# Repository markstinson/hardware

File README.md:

Internal OPL3 ISA 8 bits

version 1.0

With problems still unidentified. The schematic is based on texelec board Resound v1.1:

https://texelec.com/product/resound-opl3-4-channel-opl3-sound-card-8-bit-isa/

Symptoms:

The first start is always correct, it works and you can hear it perfectly, clear FM OPL3 sound ... but after approximately 2 minutes, it stops working. Normally a sleep period without connecting makes it work again, but there have been cases in which it stops working forever... it seems some kind of overload.

The ICs or components do not look hot, and the voltage tracks are not larger than the rest of the signals, this could be an error, however the width of the same should be sufficient for the mA demand of the ICs (I think) .

Another theory is that I do not use electrolytic 10uF capacitors as in the original design, they are 10uF without polarity, but in principle I think that should not affect the operation.

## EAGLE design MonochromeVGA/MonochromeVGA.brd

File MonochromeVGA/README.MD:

# Description

MonochromeVGA is a product to enjoy the charm of those monochrome monitors of the time but in the current video systems, and more specifically in your PC monitor. Although it could be connected to any TV, monitor or video system that has VGA inputs.

Select green, amber or B&W as monochromatic color, among others. Change color to monochrome or vice versa easily.

https://hackaday.io/project/166041-monochromevga

Disclaimer:

It is recommended to use MonochromeVGA inside an shielded container, which can be as simple as a cardboard box lined with aluminium foil, because although unlikely, the VGA signal could interfere with other nearby devices and depending on the laws of your country, it could lead to fines.

In any case, use any hardware posted here at your own risk.

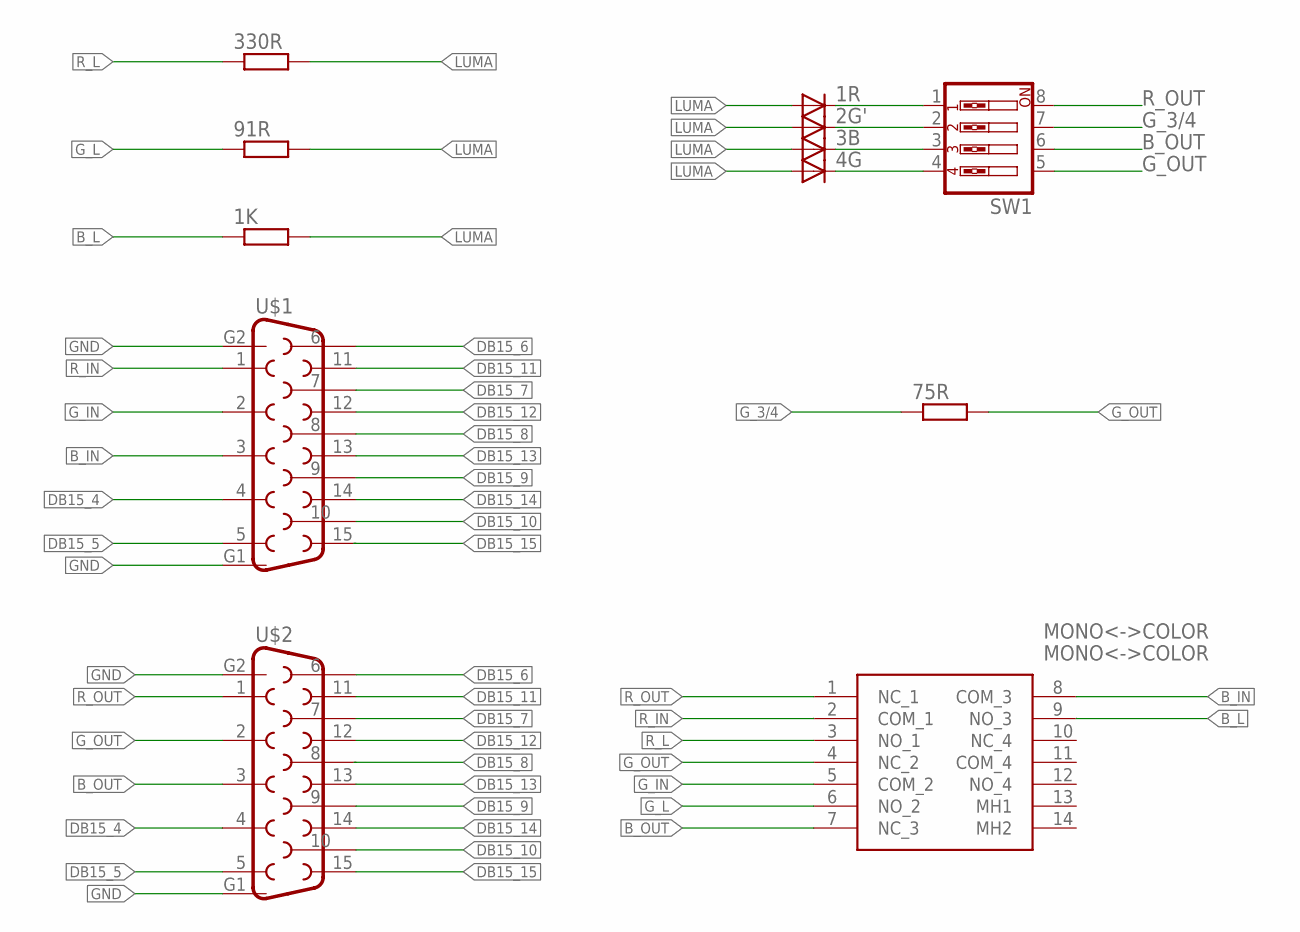
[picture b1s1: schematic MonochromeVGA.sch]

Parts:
1K, 75R, 91R, 330R: R-EU_0204/5; 0204/5
1R, 2G', 3B, 4G: DIODE-D-5; D-5
MONO<->COLOR: MONO<->COLOR; EG4208A
SW1: SW_DIP-4; EDG-04
U$1, U$2: DB15

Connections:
B_IN: MONO<->COLOR.8 (COM_3), U$1.3
B_L: 1K.1, MONO<->COLOR.9 (NO_3)
B_OUT: MONO<->COLOR.7 (NC_3), SW1.6, U$2.3
DB15_4: U$1.4, U$2.4
DB15_5: U$1.5, U$2.5
DB15_6: U$1.6, U$2.6
DB15_7: U$1.7, U$2.7
DB15_8: U$1.8, U$2.8
DB15_9: U$1.9, U$2.9
DB15_10: U$1.10, U$2.10
DB15_11: U$1.11, U$2.11
DB15_12: U$1.12, U$2.12
DB15_13: U$1.13, U$2.13
DB15_14: U$1.14, U$2.14
DB15_15: U$1.15, U$2.15
GND: U$1.G1 (G2), U$1.G2 (G1), U$2.G1 (G2), U$2.G2 (G1)
G_3/4: 75R.1, SW1.7
G_IN: MONO<->COLOR.5 (COM_2), U$1.2
G_L: 91R.1, MONO<->COLOR.6 (NO_2)
G_OUT: 75R.2, MONO<->COLOR.4 (NC_2), SW1.5, U$2.2
LUMA: 1K.2, 1R.A, 2G'.A, 3B.A, 4G.A, 91R.2, 330R.2
unnamed: 2G'.C, SW1.2
unnamed: 3B.C, SW1.3
unnamed: 4G.C, SW1.4
unnamed: 1R.C, SW1.1
R_IN: MONO<->COLOR.2 (COM_1), U$1.1
R_L: 330R.1, MONO<->COLOR.3 (NO_1)
R_OUT: MONO<->COLOR.1 (NC_1), SW1.8, U$2.1

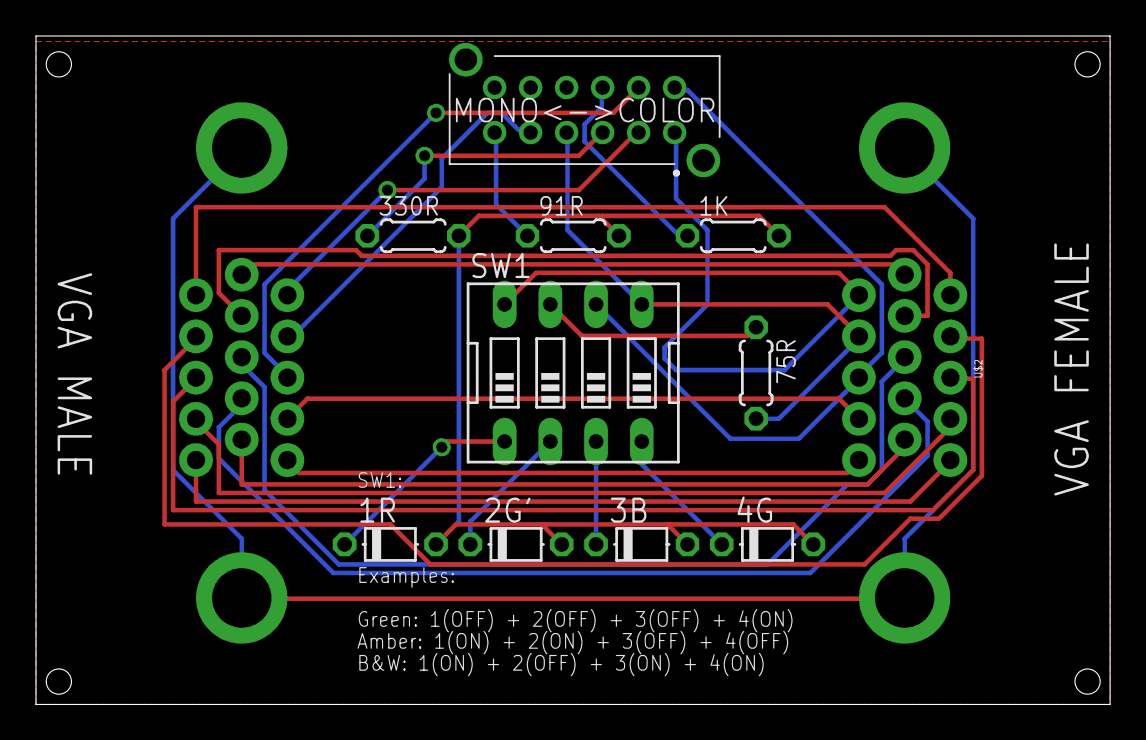
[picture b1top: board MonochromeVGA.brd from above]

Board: 2 copper layers, 59.7 x 37.1 mm, 12 parts (1 on the bottom side), 28 nets.

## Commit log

2019-07-02 Disclaimer
2019-10-12 Update to version with diodes
2019-12-21 RTC8088
    RTC8088 Kicad project, gerbers and SPLD files.
2020-01-02 Delete MonochromeVGA.brd
    It has a issue in the design of the board, pending correction ... I add the right gerbers.
2020-01-02 I add gerbers
2020-07-09 v1.2
    Diode is added between GND and VBAT for correct detection of absence of battery.

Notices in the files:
parts and their libraries:
SparkFun-Connectors: Licensing: Creative Commons ShareAlike 4.0 International - https://creativecommons.org/licenses/by-sa/4.0
